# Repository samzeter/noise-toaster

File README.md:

# MFOS noise toaster

See my website for more info

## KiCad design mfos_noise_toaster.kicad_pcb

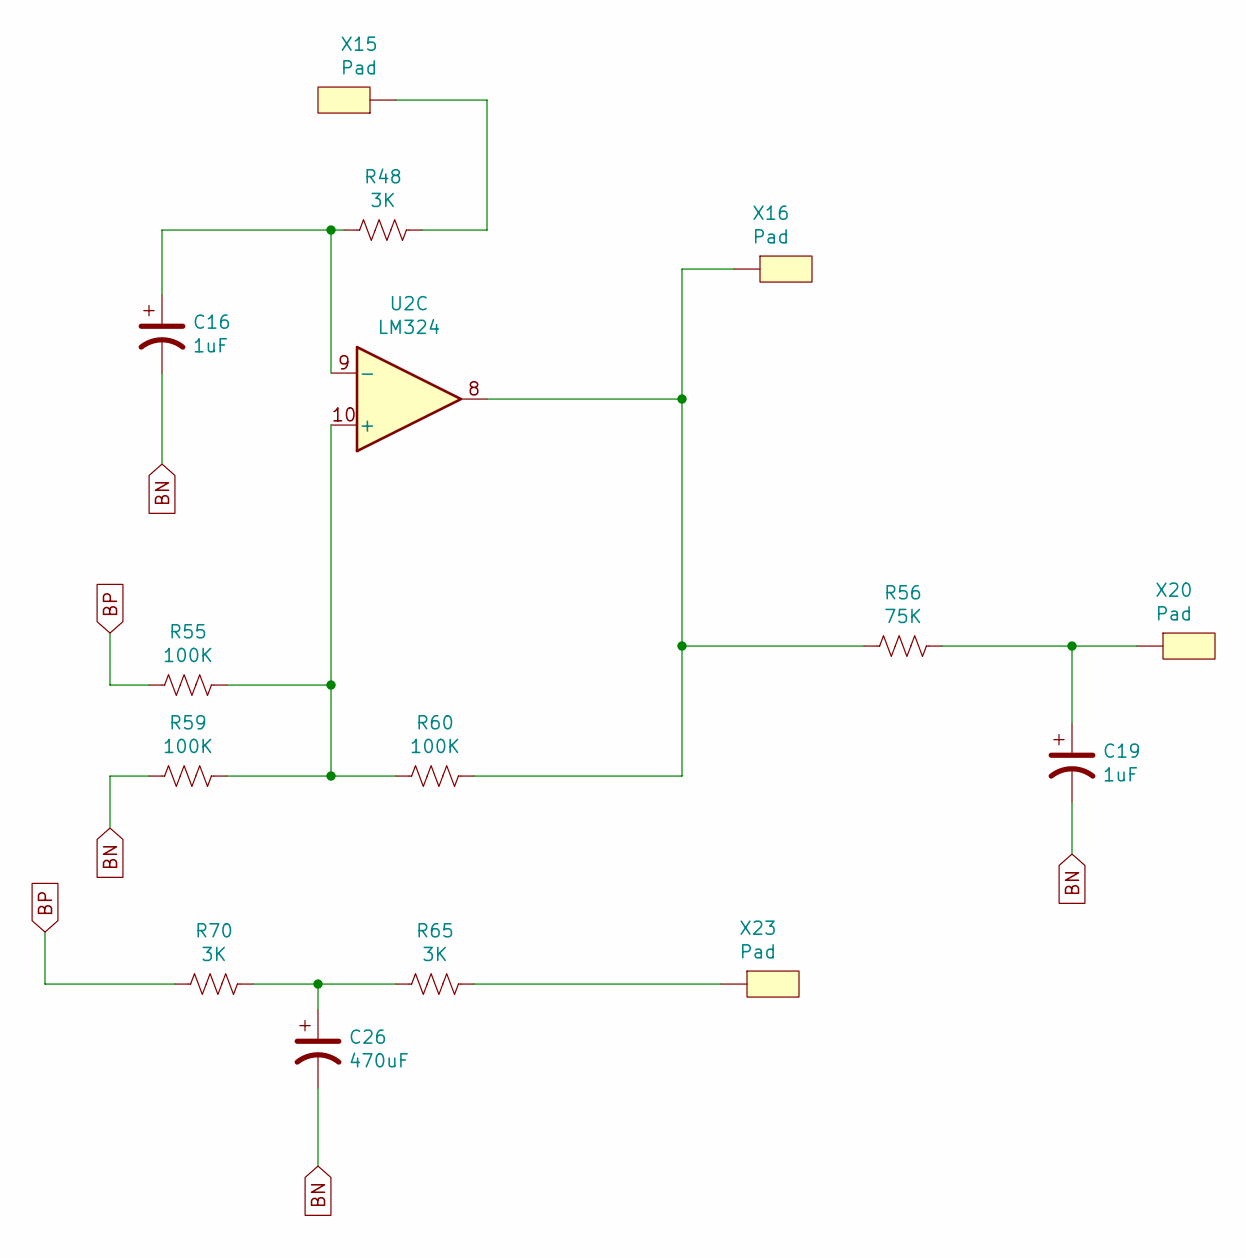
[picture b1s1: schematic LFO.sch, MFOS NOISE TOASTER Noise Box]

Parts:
C16, C19: 1uF; CP_Radial_D5.0mm_P2.50mm
C26: 470uF; CP_Radial_D10.0mm_P5.00mm
R48, R65, R70: 3K; R_Axial_DIN0207_L6.3mm_D2.5mm_P10.16mm_Horizontal
R55, R59, R60: 100K; R_Axial_DIN0207_L6.3mm_D2.5mm_P10.16mm_Horizontal
R56: 75K; R_Axial_DIN0207_L6.3mm_D2.5mm_P10.16mm_Horizontal
U2: LM324; DIP-14_W7.62mm_LongPads
X15, X16, X20, X23: Pad; pad

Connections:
BN: C16.2, C19.2, C26.2, R59.2; also elsewhere on the board
BP: R55.2, R70.2; also elsewhere on the board
unnamed: C16.1, R48.2, U2.9 (-)
unnamed: C19.1, R56.1, X20.1
unnamed: C26.1, R65.2, R70.1
unnamed: R48.1, X15.1
unnamed: R55.1, R59.1, R60.2, U2.10 (+)
unnamed: R56.2, R60.1, U2.8, X16.1
unnamed: R65.1, X23.1

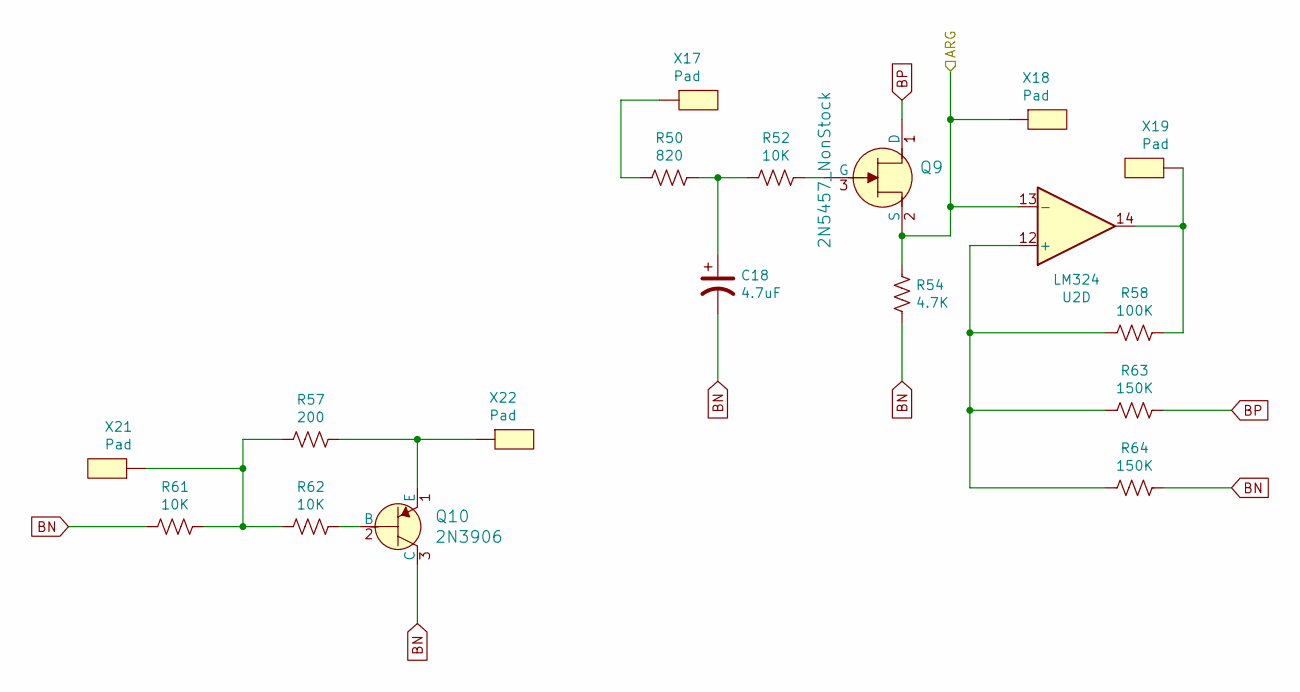
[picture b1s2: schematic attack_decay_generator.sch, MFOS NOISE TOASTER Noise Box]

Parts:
C18: 4.7uF; CP_Radial_D5.0mm_P2.50mm
Q9: 2N5457_NonStock; TO-92-3; MPN 2N5457; Digi-Key_PN 2N5457-ND
Q10: 2N3906; TO-92-3; MPN 2N3906; Digi-Key_PN 2N3906CS-ND
R50: 820; R_Axial_DIN0207_L6.3mm_D2.5mm_P10.16mm_Horizontal
R52, R61, R62: 10K; R_Axial_DIN0207_L6.3mm_D2.5mm_P10.16mm_Horizontal
R54: 4.7K; R_Axial_DIN0207_L6.3mm_D2.5mm_P10.16mm_Horizontal
R57: 200; R_Axial_DIN0207_L6.3mm_D2.5mm_P10.16mm_Horizontal
R58: 100K; R_Axial_DIN0207_L6.3mm_D2.5mm_P10.16mm_Horizontal
R63, R64: 150K; R_Axial_DIN0207_L6.3mm_D2.5mm_P10.16mm_Horizontal
U2: LM324; DIP-14_W7.62mm_LongPads
X17, X18, X19, X21, X22: Pad; pad

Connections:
/attack_decay_generator/ARG: Q9.2 (S), R54.2, U2.13 (-), X18.1; also elsewhere on the board
BN: C18.2, Q10.3 (C), R54.1, R61.2, R64.1; also elsewhere on the board
BP: Q9.1 (D), R63.1; also elsewhere on the board
unnamed: C18.1, R50.1, R52.2
unnamed: Q9.3 (G), R52.1
unnamed: Q10.1 (E), R57.1, X22.1
unnamed: Q10.2 (B), R62.1
unnamed: R50.2, X17.1
unnamed: R57.2, R61.1, R62.2, X21.1
unnamed: R58.1, U2.14, X19.1
unnamed: R58.2, R63.2, R64.2, U2.12 (+)

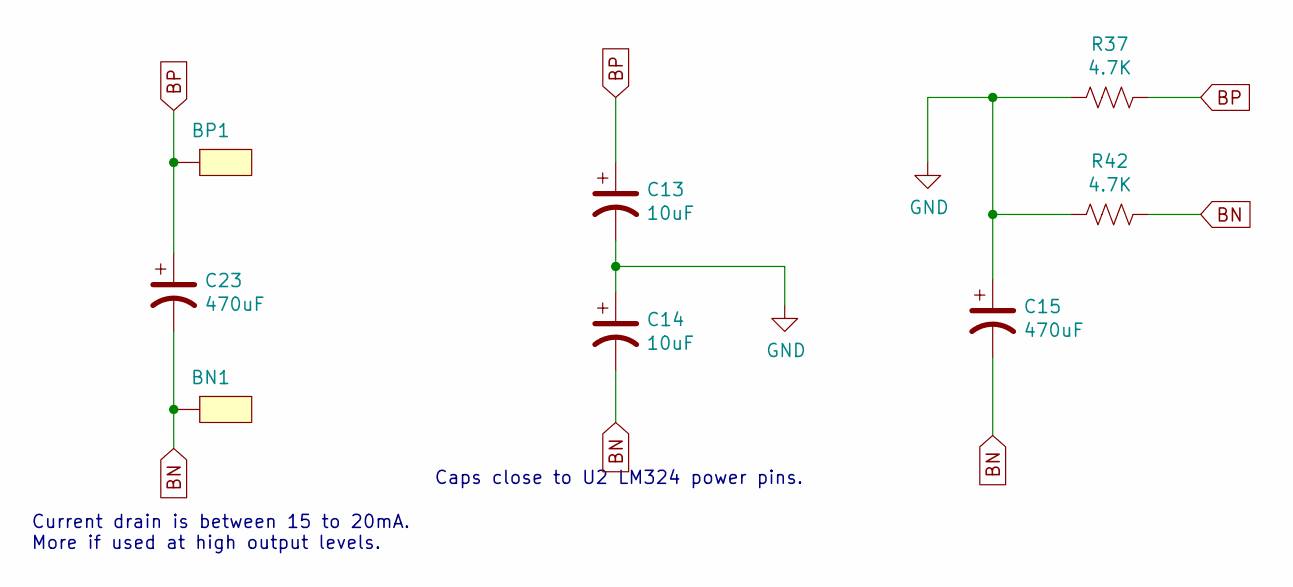
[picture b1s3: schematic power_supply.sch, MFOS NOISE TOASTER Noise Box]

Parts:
BN1: Pad-samz-symbol; pad
BP1: Pad-samz-symbol; pad
C13, C14: 10uF; CP_Radial_D5.0mm_P2.50mm
C15, C23: 470uF; CP_Radial_D10.0mm_P5.50mm
R37, R42: 4.7K; R_Axial_DIN0207_L6.3mm_D2.5mm_P10.16mm_Horizontal

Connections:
BN: BN1.1, C14.2, C15.2, C23.2, R42.1; also elsewhere on the board
BP: BP1.1, C13.1, C23.1, R37.1; also elsewhere on the board
GND: C13.2, C14.1, C15.1, R37.2, R42.2; also elsewhere on the board

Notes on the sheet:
Caps close to U2 LM324 power pins.
Current drain is between 15 to 20mA. More if used at high output levels.

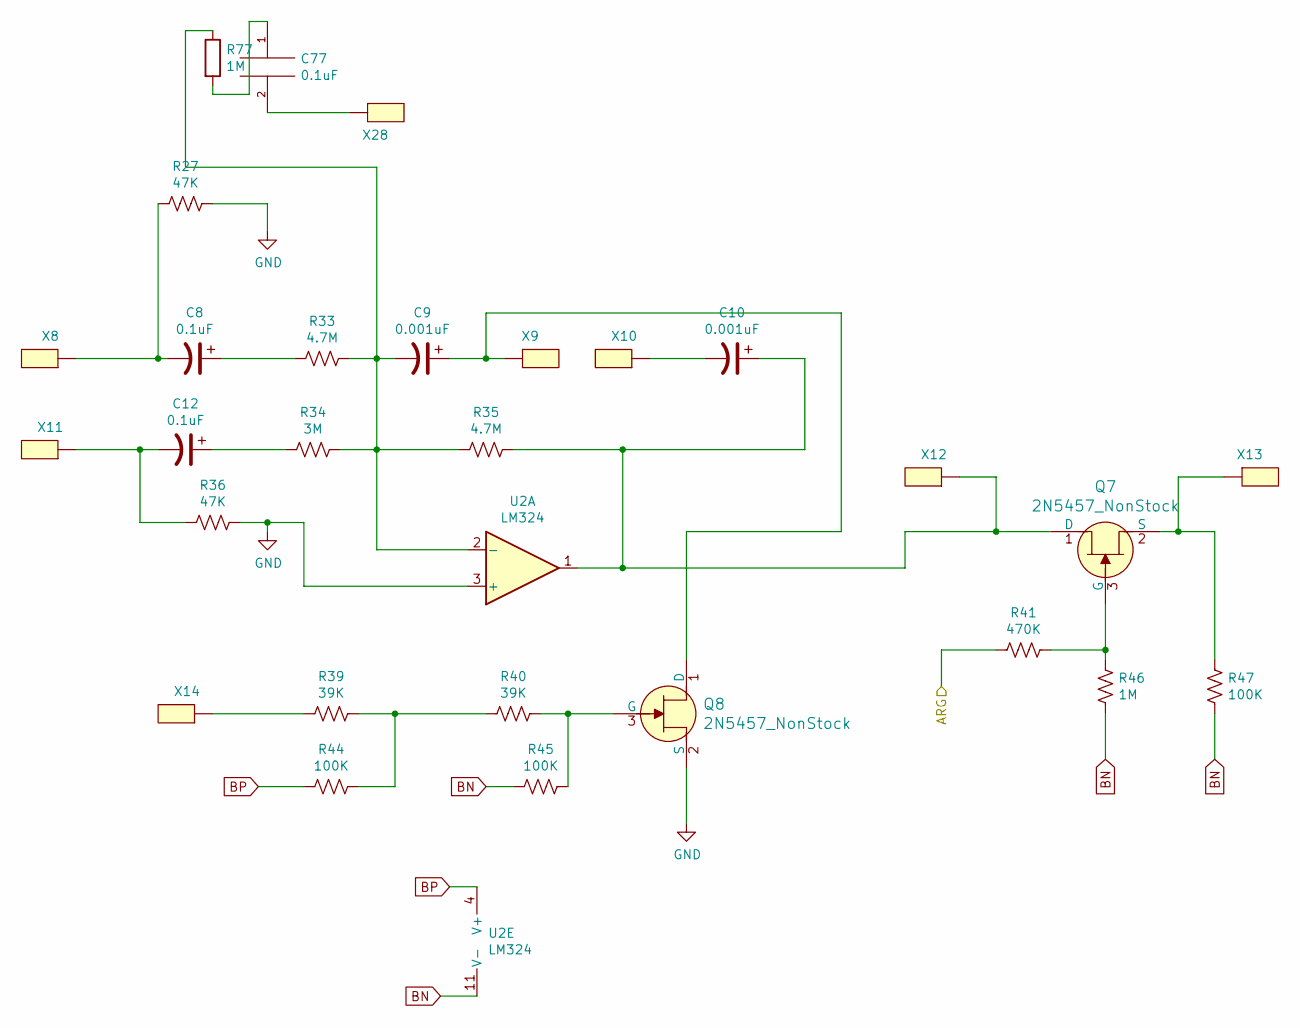
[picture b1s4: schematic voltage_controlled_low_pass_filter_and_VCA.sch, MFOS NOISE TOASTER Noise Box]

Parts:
C8, C12, C77: 0.1uF; C_Disc_D5.0mm_W2.5mm_P3.50mm
C9, C10: 0.001uF; C_Disc_D4.7mm_W2.5mm_P3.00mm
Q7, Q8: 2N5457_NonStock; TO-92-3; MPN 2N5457; Digi-Key_PN 2N5457-ND
R27, R36: 47K; R_Axial_DIN0207_L6.3mm_D2.5mm_P10.16mm_Horizontal
R33, R35: 4.7M; R_Axial_DIN0207_L6.3mm_D2.5mm_P10.16mm_Horizontal
R34: 3M; R_Axial_DIN0207_L6.3mm_D2.5mm_P10.16mm_Horizontal
R39, R40: 39K; R_Axial_DIN0207_L6.3mm_D2.5mm_P10.16mm_Horizontal
R41: 470K; R_Axial_DIN0207_L6.3mm_D2.5mm_P10.16mm_Horizontal
R44, R45, R47: 100K; R_Axial_DIN0207_L6.3mm_D2.5mm_P10.16mm_Horizontal
R46, R77: 1M; R_Axial_DIN0207_L6.3mm_D2.5mm_P10.16mm_Horizontal
U2: LM324; DIP-14_W7.62mm_LongPads
VCFinput: Pad; pad
X8, X9, X10, X11, X12, X13, X14: Pad; pad

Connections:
/attack_decay_generator/ARG: R41.1; also elsewhere on the board
BN: R45.2, R46.1, R47.1, U2.11 (V-); also elsewhere on the board
BP: R44.2, U2.4 (V+); also elsewhere on the board
GND: Q8.2 (S), R27.1, R36.1, U2.3 (+); also elsewhere on the board
unnamed: C8.1, R33.2
unnamed: C8.2, R27.2, X8.1
unnamed: C9.1, Q8.1 (D), X9.1
unnamed: C9.2, R33.1, R34.1, R35.2, R77.1, U2.2 (-)
unnamed: C10.1, Q7.1 (D), R35.1, U2.1, X12.1
unnamed: C10.2, X10.1
unnamed: C12.1, R34.2
unnamed: C12.2, R36.2, X11.1
unnamed: C77.1, R77.2
unnamed 35: C77.2; also elsewhere on the board
unnamed: Q7.2 (S), R47.2, X13.1
unnamed: Q7.3 (G), R41.2, R46.2
unnamed: Q8.3 (G), R40.1, R45.1
unnamed: R39.1, R40.2, R44.1
unnamed: R39.2, X14.1

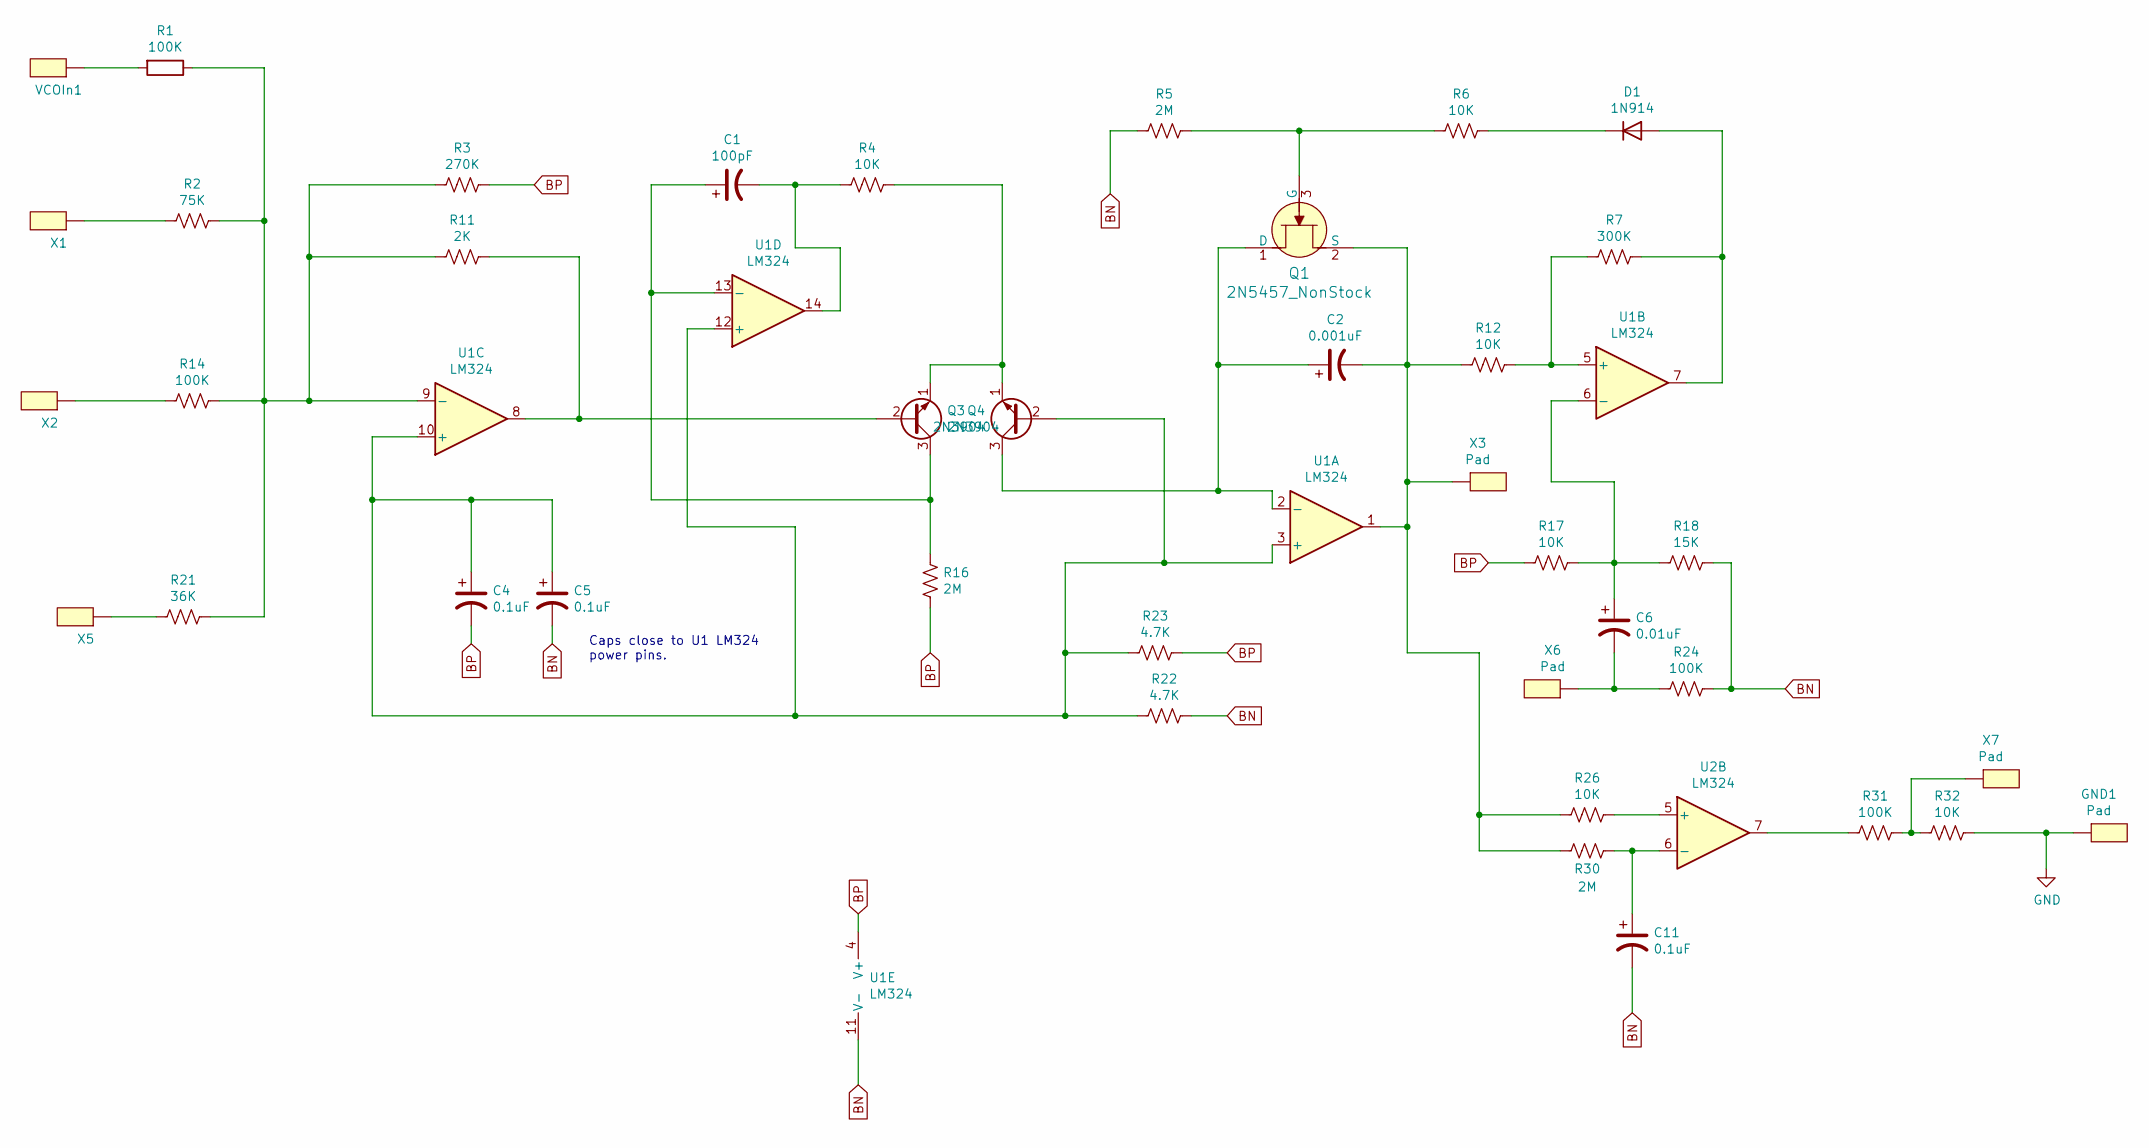
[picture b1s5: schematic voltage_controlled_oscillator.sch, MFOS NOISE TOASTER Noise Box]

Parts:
C1: 100pF; C_Disc_D3.4mm_W2.1mm_P2.50mm
C2: 0.001uF; C_Disc_D4.7mm_W2.5mm_P3.00mm
C4, C5, C11: 0.1uF; C_Disc_D5.0mm_W2.5mm_P3.50mm
C6: 0.01uF; C_Disc_D3.8mm_W2.6mm_P2.50mm
D1: 1N914; D_DO-35_SOD27_P7.62mm_Horizontal
GND1: Pad; pad
Q1: 2N5457_NonStock; TO-92-3; MPN 2N5457; Digi-Key_PN 2N5457-ND
Q3, Q4: 2N3904; TO-92_Inline
R1, R14, R24, R31: 100K; R_Axial_DIN0207_L6.3mm_D2.5mm_P10.16mm_Horizontal
R2: 75K; R_Axial_DIN0207_L6.3mm_D2.5mm_P10.16mm_Horizontal
R3: 270K; R_Axial_DIN0207_L6.3mm_D2.5mm_P10.16mm_Horizontal
R4, R6, R12, R17, R26, R32: 10K; R_Axial_DIN0207_L6.3mm_D2.5mm_P10.16mm_Horizontal
R5, R16, R30: 2M; R_Axial_DIN0207_L6.3mm_D2.5mm_P10.16mm_Horizontal
R7: 300K; R_Axial_DIN0207_L6.3mm_D2.5mm_P10.16mm_Horizontal
R11: 2K; R_Axial_DIN0207_L6.3mm_D2.5mm_P10.16mm_Horizontal
R18: 15K; R_Axial_DIN0207_L6.3mm_D2.5mm_P10.16mm_Horizontal
R21: 36K; R_Axial_DIN0207_L6.3mm_D2.5mm_P10.16mm_Horizontal
R22, R23: 4.7K; R_Axial_DIN0207_L6.3mm_D2.5mm_P10.16mm_Horizontal
U1, U2: LM324; DIP-14_W7.62mm_LongPads
VCOIn1: Pad; pad
X1, X2, X3, X5, X6, X7: Pad; pad

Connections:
BN: C5.2, C11.2, R5.2, R18.1, R22.1, R24.1, U1.11 (V-); also elsewhere on the board
BP: C4.2, R3.1, R16.2, R17.2, R23.1, U1.4 (V+); also elsewhere on the board
GND: GND1.1, R32.1; also elsewhere on the board
unnamed: C1.1, Q3.3 (C), R16.1, U1.13 (-)
unnamed: C1.2, R4.2, U1.14
unnamed: C2.1, Q1.1 (D), Q4.3 (C), U1.2 (-)
unnamed: C2.2, Q1.2 (S), R12.2, R26.2, R30.2, U1.1, X3.1
unnamed: C4.1, C5.1, Q4.2 (B), R22.2, R23.2, U1.3 (+), U1.10 (+), U1.12 (+)
unnamed: C6.1, R17.1, R18.2, U1.6 (-)
unnamed: C6.2, R24.2, X6.1
unnamed: C11.1, R30.1, U2.6 (-)
unnamed: D1.1 (K), R6.1
unnamed: D1.2 (A), R7.1, U1.7
unnamed: Q1.3 (G), R5.1, R6.2
unnamed: Q3.1 (E), Q4.1 (E), R4.1
unnamed: Q3.2 (B), R11.1, U1.8
unnamed: R1.1, R2.1, R3.2, R11.2, R14.1, R21.1, U1.9 (-)
unnamed: R1.2, VCOIn1.1
unnamed: R2.2, X1.1
unnamed: R7.2, R12.1, U1.5 (+)
unnamed: R14.2, X2.1
unnamed: R21.2, X5.1
unnamed: R26.1, U2.5 (+)
unnamed: R31.1, R32.2, X7.1
unnamed: R31.2, U2.7

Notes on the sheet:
Caps close to U1 LM324 power pins.

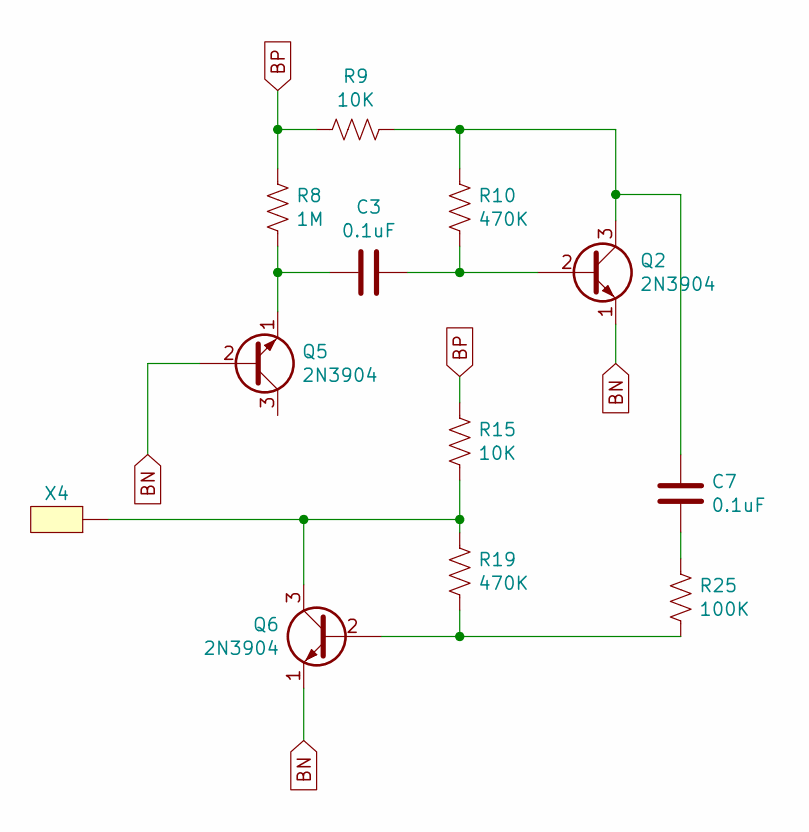
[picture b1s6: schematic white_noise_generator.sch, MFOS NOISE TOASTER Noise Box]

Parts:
C3, C7: 0.1uF; C_Disc_D5.0mm_W2.5mm_P3.50mm
Q2, Q5, Q6: 2N3904; TO-92_Inline
R8: 1M; R_Axial_DIN0207_L6.3mm_D2.5mm_P10.16mm_Horizontal
R9, R15: 10K; R_Axial_DIN0207_L6.3mm_D2.5mm_P10.16mm_Horizontal
R10, R19: 470K; R_Axial_DIN0207_L6.3mm_D2.5mm_P10.16mm_Horizontal
R25: 100K; R_Axial_DIN0207_L6.3mm_D2.5mm_P10.16mm_Horizontal
X4: Pad; pad

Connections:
BN: Q2.1 (E), Q5.2 (B), Q6.1 (E); also elsewhere on the board
BP: R8.1, R9.2, R15.1; also elsewhere on the board
unnamed: C3.1, Q2.2 (B), R10.2
unnamed: C3.2, Q5.1 (E), R8.2
unnamed: C7.1, R25.1
unnamed: C7.2, Q2.3 (C), R9.1, R10.1
unnamed: Q6.2 (B), R19.2, R25.2
unnamed: Q6.3 (C), R15.2, R19.1, X4.1

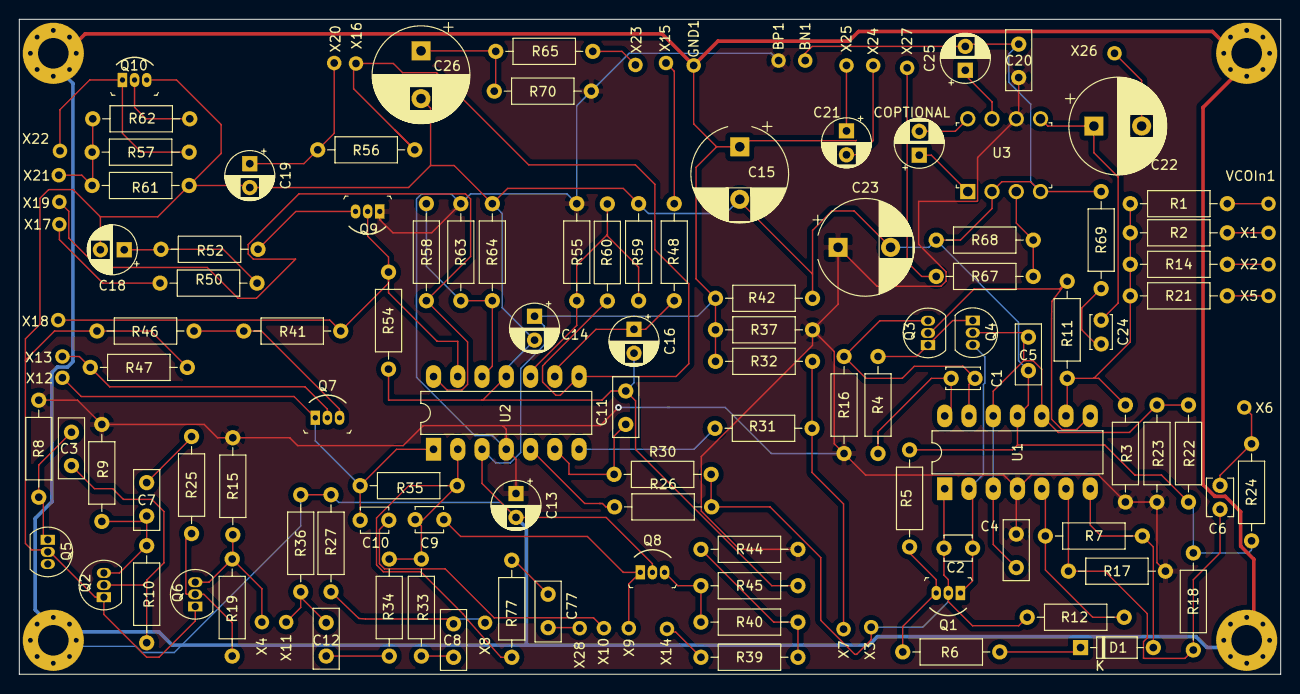
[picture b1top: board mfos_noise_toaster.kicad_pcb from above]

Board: 2 copper layers, 132.1 x 68.6 mm, 134 parts (0 on the bottom side), 72 nets.

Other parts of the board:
C20: 0.1uF; C_Disc_D5.0mm_W2.5mm_P3.50mm
C21: 1uF; CP_Radial_D5.0mm_P2.50mm
C22: 220uF; CP_Radial_D10.0mm_P5.00mm
C24: 0.047uF; C_Disc_D3.4mm_W2.1mm_P2.50mm
C25: 10uF; CP_Radial_D5.0mm_P2.50mm
COPTIONAL: 10uF; CP_Radial_D5.0mm_P2.50mm
R67: 100K; R_Axial_DIN0207_L6.3mm_D2.5mm_P10.16mm_Horizontal
R68: 20K; R_Axial_DIN0207_L6.3mm_D2.5mm_P10.16mm_Horizontal
R69: 10; R_Axial_DIN0207_L6.3mm_D2.5mm_P10.16mm_Horizontal
U3: LM386N-4_NOPB; DIP-8_W7.62mm
X24, X25, X26, X27, X28: Pad; pad

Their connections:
BN: C20.2, C25.2, R68.2, R69.2, U3.2, U3.4; also elsewhere on the board
BP: C20.1, U3.6; also elsewhere on the board
unnamed: C21.1, X25.1
unnamed: C21.2, X24.1
unnamed: C22.1, C24.1, U3.5
unnamed: C22.2, X26.1
unnamed: C24.2, R69.1
unnamed: C25.1, U3.7
unnamed 35: X28.1; also elsewhere on the board
unnamed: COPTIONAL.1, U3.1
unnamed: COPTIONAL.2, U3.8
unnamed: R67.1, R68.1, U3.3
unnamed: R67.2, X27.1

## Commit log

2021-05-30 first
